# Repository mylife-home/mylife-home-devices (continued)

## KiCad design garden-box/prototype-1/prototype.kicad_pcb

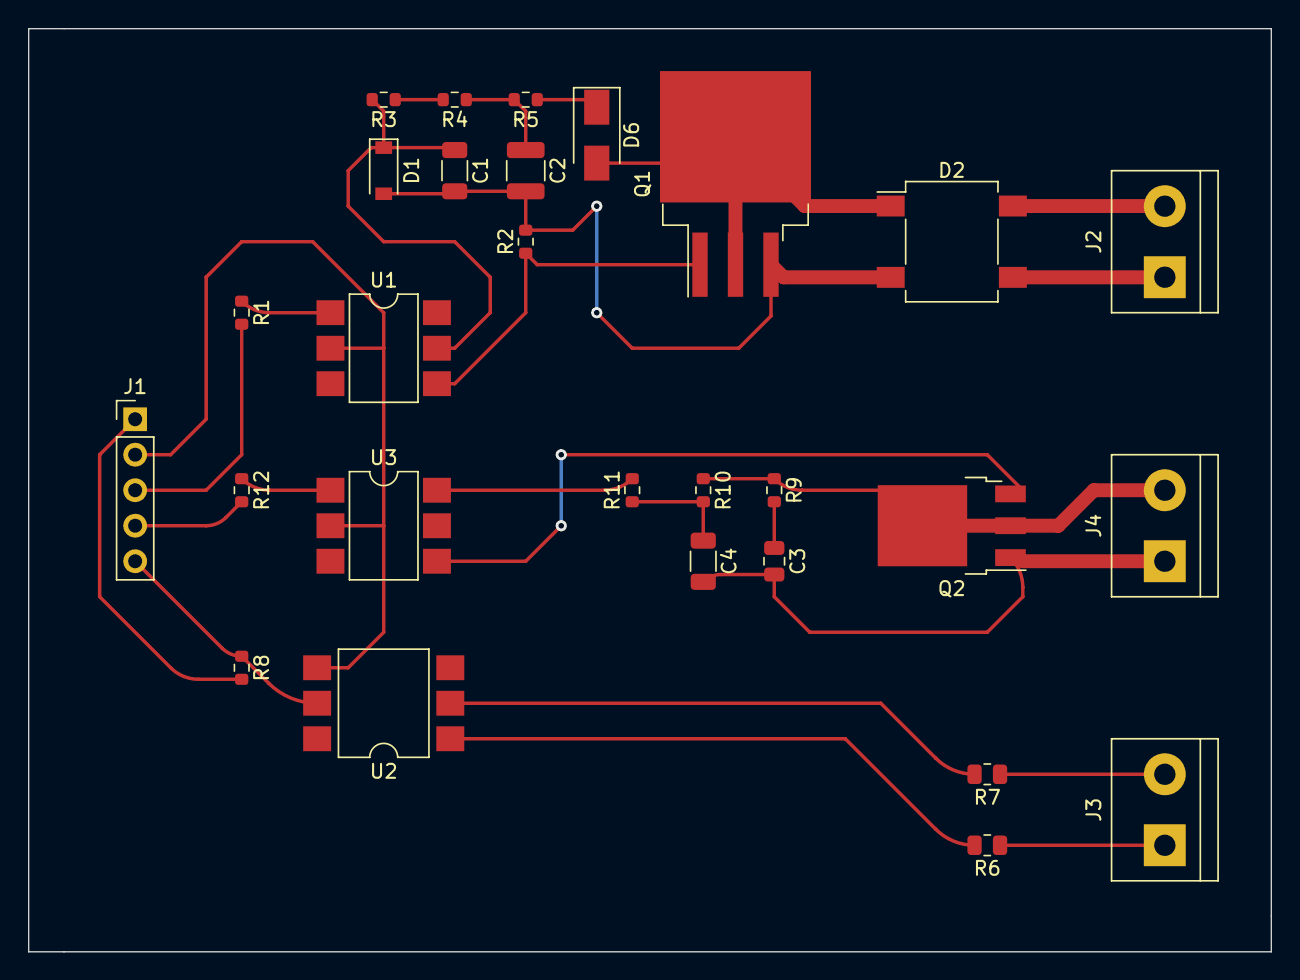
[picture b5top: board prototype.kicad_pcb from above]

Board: 2 copper layers, 88.9 x 66.0 mm, 28 parts (0 on the bottom side), 26 nets.

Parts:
C1: 2.2uF/63V; C_1206_3216Metric
C2: 220nF/275V; C_1210_3225Metric
C3: 10nF; C_0805_2012Metric
C4: 47nF; C_1206_3216Metric
D1: 10V/0.4W; D_SOD-123
D2: 4* 1N5408; Diode_Bridge_Diotec_SO-DIL-Slim
D6: 1N4007; D_SMA
J1: Conn_01x05_Male; PinHeader_1x05_P2.54mm_Vertical
J2, J3, J4: Screw_Terminal_01x02; TerminalBlock_bornier-2_P5.08mm
Q1: IRF830; TO-263-3_TabPin2
Q2: BT136-600; TO-252-3_TabPin2
R1: 330Ω; R_0603_1608Metric
R2: 22KΩ; R_0603_1608Metric
R3, R4: 33KΩ; R_0603_1608Metric
R5, R12: 220Ω; R_0603_1608Metric
R6, R7: 33KΩ/0.5W; R_0805_2012Metric
R8: 10KΩ; R_0603_1608Metric
R9: 39Ω; R_0603_1608Metric
R10: 470Ω; R_0603_1608Metric
R11: 360Ω; R_0603_1608Metric
U1: 4N35; SMDIP-6_W7.62mm
U2: H11AA1; SMDIP-6_W9.53mm
U3: MOC3021M; SMDIP-6_W7.62mm

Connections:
+3V3: J1.1, R8.2
GND: J1.2, U1.2, U2.4, U3.2
unnamed: C1.1, D1.1 (K), R3.2, U1.5
unnamed: C1.2, C2.2, D1.2 (A), D2.2 (-), Q1.3 (S), R2.2
unnamed: C2.1, R4.1, R5.2
unnamed: C3.1, R9.2
unnamed: C3.2, C4.2, J4.1, Q2.1 (A1)
unnamed: C4.1, R10.2, R11.1
unnamed: D2.1 (+), D6.2 (A), Q1.2 (D)
unnamed: D2.3, J2.1
unnamed: D2.4, J2.2
unnamed: D6.1 (K), R5.1
unnamed: J1.3, R1.2
unnamed: J1.4, R12.2
unnamed: J1.5, R8.1, U2.5
unnamed: J3.1, R6.1
unnamed: J3.2, R7.1
unnamed: Q1.1 (G), R2.1, U1.4
unnamed: J4.2, Q2.2 (A2), R9.1, R10.1
unnamed: Q2.3 (G), U3.4
unnamed: R1.1, U1.1
unnamed: R3.1, R4.2
unnamed: R6.2, U2.1
unnamed: R7.2, U2.2
unnamed: R11.2, U3.6
unnamed: R12.1, U3.1
